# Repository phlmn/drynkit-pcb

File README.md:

# drynk.it PCB

## Repository Structure

| Folder     | Description                     |
| ---------- | ------------------------------- |
| board      | The KiCAD files for the PCB     |
| bugs       | Known bugs and fixes for boards |
| datasheets | Relevant datasheets             |

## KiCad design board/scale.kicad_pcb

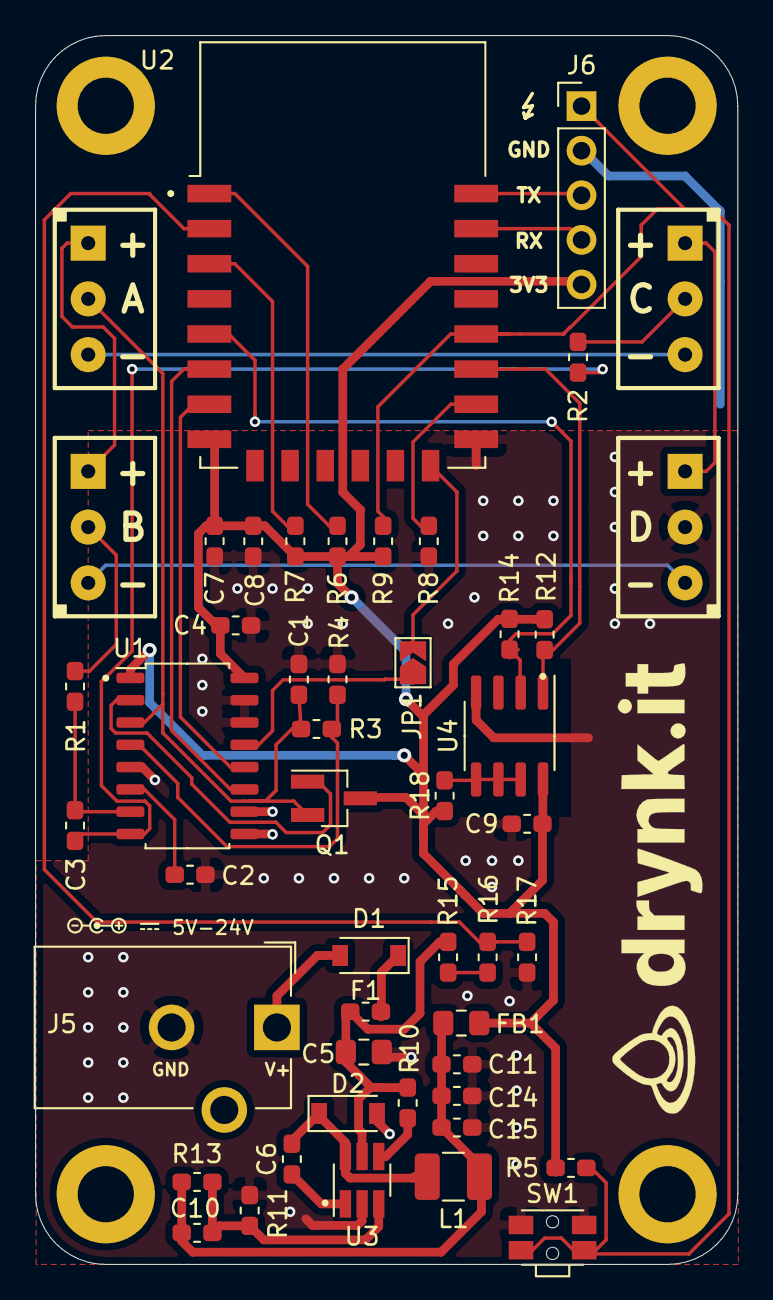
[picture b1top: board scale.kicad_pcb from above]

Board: 2 copper layers, 40.0 x 70.0 mm, 49 parts (0 on the bottom side), 37 nets.

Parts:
C1, C4, C7, C11: 10uF; C_0603_1608Metric_Pad1.05x0.95mm_HandSolder
C2, C3, C9: 0.1uF; C_0603_1608Metric_Pad1.05x0.95mm_HandSolder
C5: 4.7uF/25V; C_0805_2012Metric_Pad1.15x1.40mm_HandSolder
C6, C8: 100nF; C_0603_1608Metric_Pad1.05x0.95mm_HandSolder
C10: 33pF; C_0603_1608Metric_Pad1.05x0.95mm_HandSolder
C14, C15: DNP; C_0603_1608Metric_Pad1.05x0.95mm_HandSolder
D1, D2: B5819W; D_SOD-123
F1: 500mA/24V (CFS06V3T1R0); Fuse_0603_1608Metric_Pad1.05x0.95mm_HandSolder
FB1: GZ2012D601TF; L_0805_2012Metric_Pad1.15x1.40mm_HandSolder
J1: Cell A; SolderWirePad_1x03_P3.175mm_Drill0.8mm
J2: Cell B; SolderWirePad_1x03_P3.175mm_Drill0.8mm
J3: Cell C; SolderWirePad_1x03_P3.175mm_Drill0.8mm
J4: Cell D; SolderWirePad_1x03_P3.175mm_Drill0.8mm
J5: Jack-DC; BarrelJack_CUI_PJ-102AH_Horizontal
J6: Conn_01x05; PinHeader_1x05_P2.54mm_Vertical
JP1: Jumper_NO_Small; SolderJumper-2_P1.3mm_Open_TrianglePad1.0x1.5mm
L1: 2.2 - 4.7uH; L_1210_3225Metric_Pad1.42x2.65mm_HandSolder
Q1: Q_PNP_BCE; SOT-23_Handsoldering
R1, R2: 100; R_0603_1608Metric_Pad1.05x0.95mm_HandSolder
R3: 20K; R_0603_1608Metric_Pad1.05x0.95mm_HandSolder
R4: 8.2K; R_0603_1608Metric_Pad1.05x0.95mm_HandSolder
R5, R6, R7, R8, R9, R10, R12, R14, R17, R18: 4.7k; R_0603_1608Metric_Pad1.05x0.95mm_HandSolder
R11: 24k; R_0603_1608Metric_Pad1.05x0.95mm_HandSolder
R13, R15, R16: 75k; R_0603_1608Metric_Pad1.05x0.95mm_HandSolder
SW1: SW_Push; SW_SPST_EVQP7C
U1: HX711; SOP-16_4.55x10.3mm_P1.27mm
U2: ESP-12E
U3: MP2451; SOT-23-6_Handsoldering
U4: LM75B; SOIC-8_3.9x4.9mm_P1.27mm

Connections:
+3V3: C4.1, C7.2, C8.2, C9.1, FB1.2, J6.5, Q1.3, R5.1, R6.2, R7.2, R9.2, R12.1, R14.2, R18.2, U1.1, U1.16, U2.8, U4.8
+VDC: D1.2, J5.1
/ADC_CLK: JP1.1, U1.13
/ADC_DOUT: U1.12, U2.7
/ADC_SCK: U1.11, U2.6
/BOOTLOADER: J6.1, R5.2, R9.1, SW1.2, U2.18
/CELL_E+: C1.1, J1.2, Q1.2, R3.1, U1.3
/CELL_S+: J3.2, R2.2
/CELL_S-: J2.2, R1.2
/RX: J6.4, U2.21
/SCL: R14.1, U2.5, U4.2
/SDA: R12.2, U2.17, U4.1
/TX: J6.3, U2.22
/V_SENSE: C5.1, F1.1, R10.2, R15.1, U3.5
GND: C1.2, C2.1, C4.2, C5.2, C7.1, C8.1, C9.2, C11.2, C14.1, C15.1, D2.2, J4.2, J5.2, J6.2, R4.2, R8.2, R11.2, R17.1, SW1.1, U1.5, U1.9, U1.10, U1.14, U1.15, U2.15, U3.2, U4.4
unnamed: C2.2, U1.6
unnamed: C3.1, R1.1, U1.7
unnamed: C3.2, R2.1, U1.8
unnamed: C6.1, U3.1
unnamed: C6.2, D2.1, L1.1, U3.6
unnamed: C10.1, C11.1, C14.2, C15.2, FB1.1, L1.2, R13.2
unnamed: C10.2, R11.1, R13.1, U3.3
unnamed: D1.1, F1.2
unnamed: J1.1, J2.1
unnamed: J1.3, J3.3
unnamed: J2.3, J4.3
unnamed: J3.1, J4.1
unnamed: JP1.2, U2.14
unnamed: Q1.1, U1.2
unnamed: R3.2, R4.1, U1.4
unnamed: R6.1, U2.1
unnamed: R7.1, U2.3
unnamed: R8.1, U2.16
unnamed: R10.1, U3.4
unnamed: R15.2, R16.2
unnamed: R16.1, R17.2, U2.2
unnamed: R18.1, U4.5, U4.6, U4.7

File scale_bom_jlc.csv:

"Comment","Designator","Footprint","LCSC Part #"
"0.1uF","C2,C3,C9","C_0603_1608Metric_Pad1.05x0.95mm_HandSolder","C14663"
"10uF","C4,C1,C7,C11","C_0603_1608Metric_Pad1.05x0.95mm_HandSolder","C19702"
"4.7uF/25V","C5","C_0805_2012Metric_Pad1.15x1.40mm_HandSolder","C1779"
"100nF","C8,C6","C_0603_1608Metric_Pad1.05x0.95mm_HandSolder","C14663"
"33pF","C10","C_0603_1608Metric_Pad1.05x0.95mm_HandSolder","C1663"
"B5819W","D1,D2","D_SOD-123","C8598"
"500mA/24V (CFS06V3T1R0)","F1","Fuse_0603_1608Metric_Pad1.05x0.95mm_HandSolder","C163118"
"GZ2012D601TF","FB1","L_0805_2012Metric_Pad1.15x1.40mm_HandSolder","C1017"
"2.2 - 4.7uH","L1","L_1210_3225Metric_Pad1.42x2.65mm_HandSolder","C86074"
"Q_PNP_BCE","Q1","SOT-23_Handsoldering","C8542"
"100","R1,R2","R_0603_1608Metric_Pad1.05x0.95mm_HandSolder","C22775"
"20K","R3","R_0603_1608Metric_Pad1.05x0.95mm_HandSolder","C4184"
"8.2K","R4","R_0603_1608Metric_Pad1.05x0.95mm_HandSolder","C25981"
"4.7k","R5,R6,R7,R9,R8,R10,R14,R12,R17","R_0603_1608Metric_Pad1.05x0.95mm_HandSolder","C23162"
"24k","R11","R_0603_1608Metric_Pad1.05x0.95mm_HandSolder","C23352"
"75k","R13,R16,R15","R_0603_1608Metric_Pad1.05x0.95mm_HandSolder","C23242"
"HX711","U1","SOP-16_4.55x10.3mm_P1.27mm","C43656"
"MP2451","U3","SOT-23-6_Handsoldering","C14123"
"LM75B","U4","SOIC-8_3.9x4.9mm_P1.27mm","C34565"

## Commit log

2020-07-10 temp: Fix floating i2c address pins
2020-07-10 Add datasheets
2020-07-10 Add known bugs
2020-07-10 i2c Bug: Add more information
2020-07-10 Add README
2020-07-19 LM75 i2c address resistor
2020-07-19 Fix polarity graphics
2020-07-19 Place resistor for TMP75
2023-12-15 Add renovate.json
